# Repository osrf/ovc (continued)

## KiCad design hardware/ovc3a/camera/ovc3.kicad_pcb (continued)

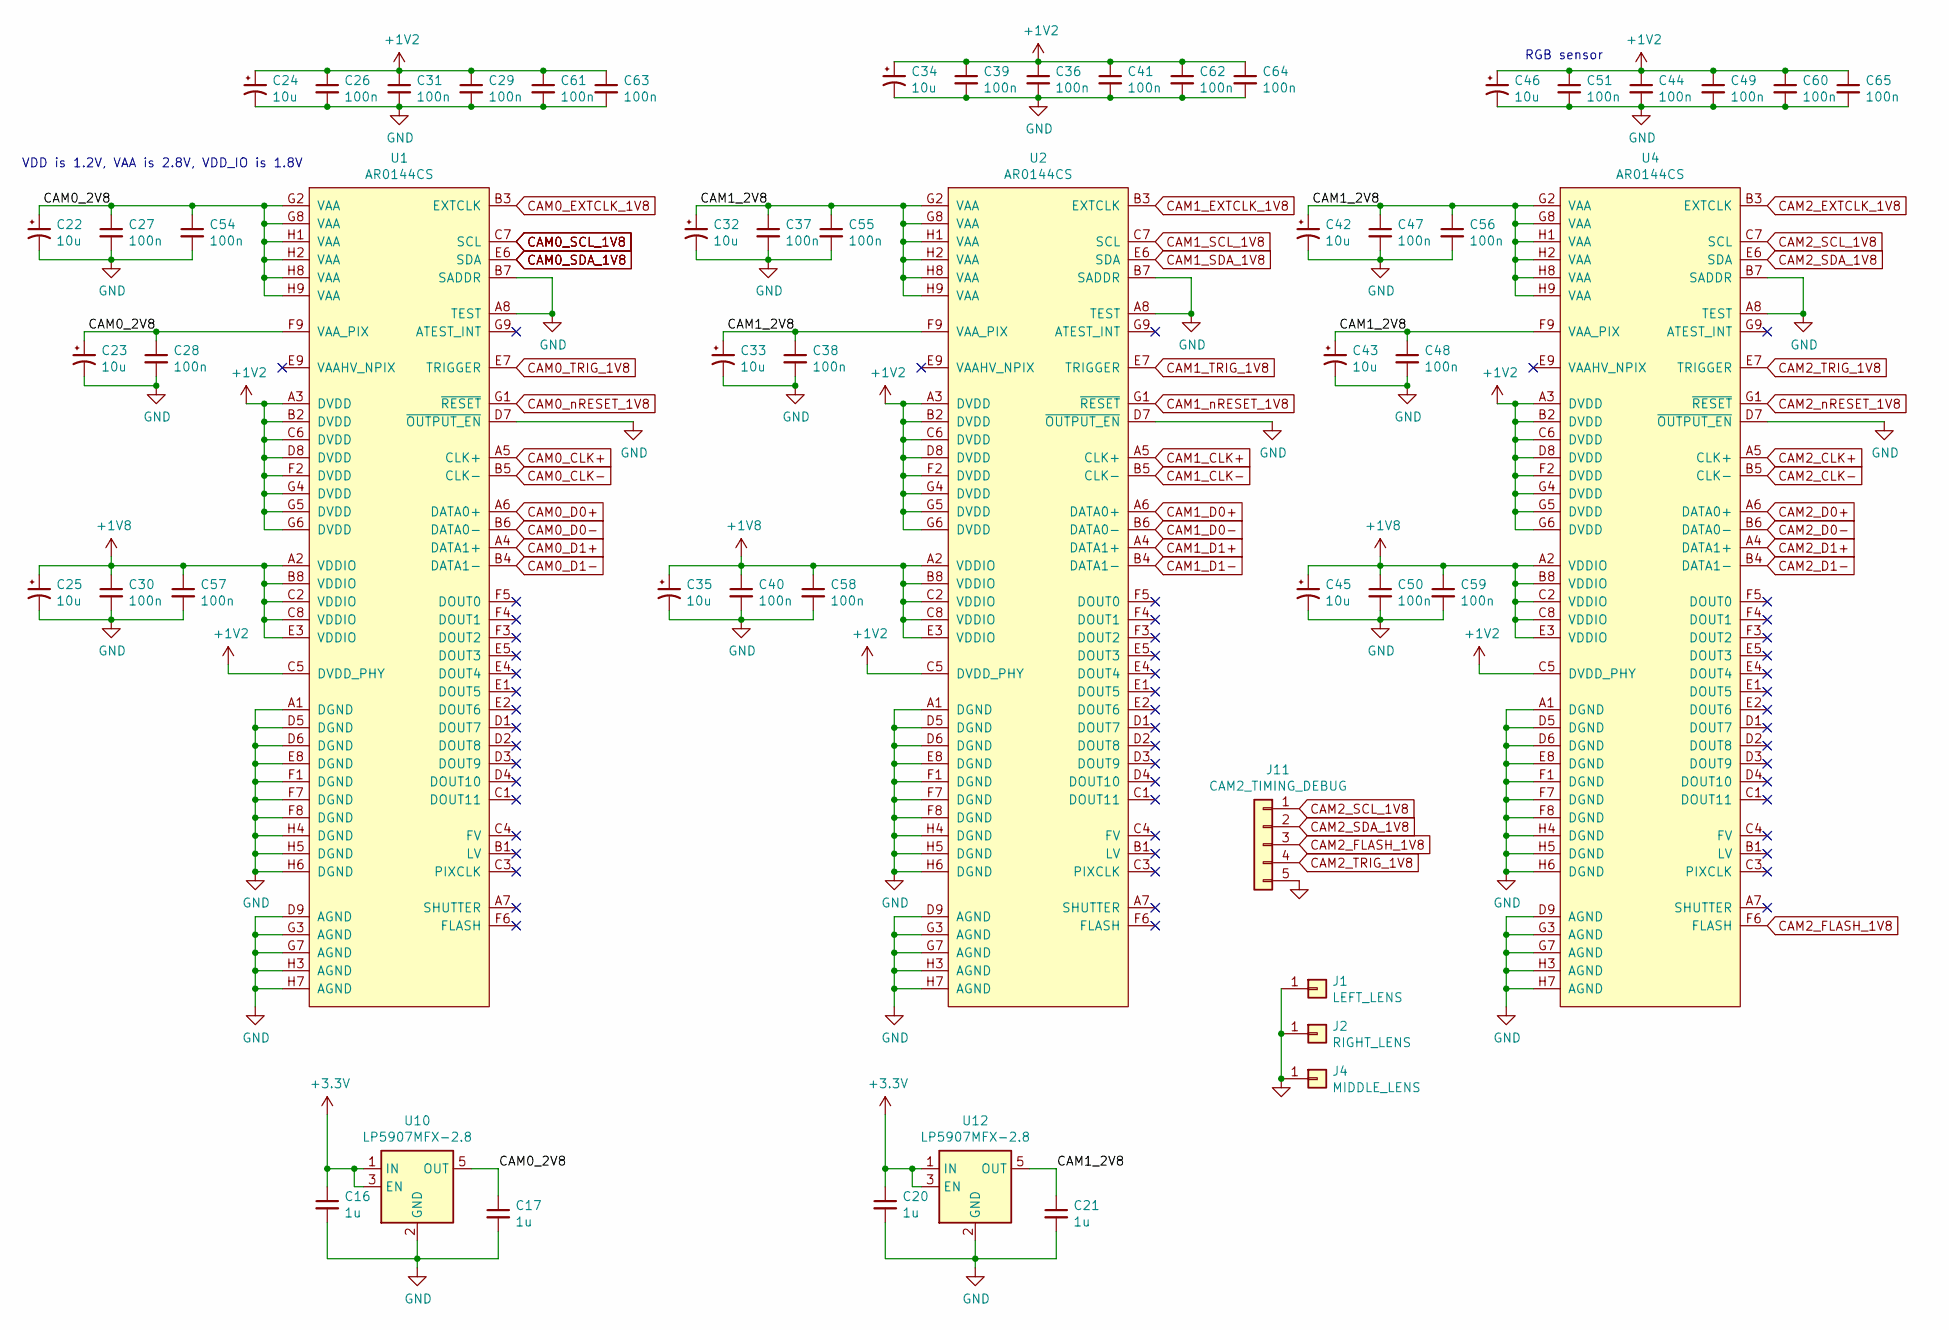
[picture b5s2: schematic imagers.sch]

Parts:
C16, C17, C20, C21: 1u; C_0402_1005Metric; MPN CL05A105KA5NQNC
C22, C23, C24, C25, C32, C33, C34, C35, C42, C43, C45, C46: 10u; C_0402_1005Metric; MPN CL05A106MP8NUB8
C26, C27, C28, C29, C30, C31, C36, C37, C38, C39, C40, C41, C44, C47, C48, C49, C50, C51, C54, C55, C56, C57, C58, C59, C60, C61, C62, C63, C64, C65: 100n; C_0402_1005Metric; MPN CL05F104ZO5NNNC
J1: LEFT_LENS; LENS_HOLDER_20MM_PT-LH010M; MPN DNP
J2: RIGHT_LENS; LENS_HOLDER_20MM_PT-LH010M; MPN DNP
J4: MIDDLE_LENS; LENS_HOLDER_20MM_PT-LH010M; MPN DNP
J11: CAM2_TIMING_DEBUG; PinHeader_1x05_P2.00mm_Vertical; MPN DNP
U1, U2: AR0144CS; BGA-72_9x8_5.545x5.565mm; MPN AR0144CSSM00SUKA0-CPBR2
U4: AR0144CS; BGA-72_9x8_5.545x5.565mm; MPN AR0144CSSC00SUKA0-CPBR2
U10, U12: LP5907MFX-2.8; SOT-23-5; MPN LP5907MFX-2.8/NOPB

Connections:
+1V2: C24.1, C26.1, C29.1, C31.1, C34.1, C36.1, C39.1, C41.1, C44.1, C46.1, C49.1, C51.1, C60.1, C61.1, C62.1, C63.1, C64.1, C65.1, U1.A3 (DVDD), U1.B2 (DVDD), U1.C5 (DVDD_PHY), U1.C6 (DVDD), U1.D8 (DVDD), U1.F2 (DVDD), U1.G4 (DVDD), U1.G5 (DVDD), U1.G6 (DVDD), U2.A3 (DVDD), U2.B2 (DVDD), U2.C5 (DVDD_PHY), U2.C6 (DVDD), U2.D8 (DVDD), U2.F2 (DVDD), U2.G4 (DVDD), U2.G5 (DVDD), U2.G6 (DVDD), U4.A3 (DVDD), U4.B2 (DVDD), U4.C5 (DVDD_PHY), U4.C6 (DVDD), U4.D8 (DVDD), U4.F2 (DVDD), U4.G4 (DVDD), U4.G5 (DVDD), U4.G6 (DVDD); also elsewhere on the board
+1V8: C25.1, C30.1, C35.1, C40.1, C45.1, C50.1, C57.1, C58.1, C59.1, U1.A2 (VDDIO), U1.B8 (VDDIO), U1.C2 (VDDIO), U1.C8 (VDDIO), U1.E3 (VDDIO), U2.A2 (VDDIO), U2.B8 (VDDIO), U2.C2 (VDDIO), U2.C8 (VDDIO), U2.E3 (VDDIO), U4.A2 (VDDIO), U4.B8 (VDDIO), U4.C2 (VDDIO), U4.C8 (VDDIO), U4.E3 (VDDIO); also elsewhere on the board
/imagers/CAM0_2V8: C17.1, C22.1, C23.1, C27.1, C28.1, C54.1, U1.F9 (VAA_PIX), U1.G2 (VAA), U1.G8 (VAA), U1.H1 (VAA), U1.H2 (VAA), U1.H8 (VAA), U1.H9 (VAA), U10.5 (OUT)
/imagers/CAM1_2V8: C21.1, C32.1, C33.1, C37.1, C38.1, C42.1, C43.1, C47.1, C48.1, C55.1, C56.1, U2.F9 (VAA_PIX), U2.G2 (VAA), U2.G8 (VAA), U2.H1 (VAA), U2.H2 (VAA), U2.H8 (VAA), U2.H9 (VAA), U4.F9 (VAA_PIX), U4.G2 (VAA), U4.G8 (VAA), U4.H1 (VAA), U4.H2 (VAA), U4.H8 (VAA), U4.H9 (VAA), U12.5 (OUT)
CAM0_CLK+: U1.A5 (CLK+); also elsewhere on the board
CAM0_CLK-: U1.B5 (CLK-); also elsewhere on the board
CAM0_D0+: U1.A6 (DATA0+); also elsewhere on the board
CAM0_D0-: U1.B6 (DATA0-); also elsewhere on the board
CAM0_D1+: U1.A4 (DATA1+)
CAM0_D1-: U1.B4 (DATA1-)
CAM0_EXTCLK_1V8: U1.B3 (EXTCLK); also elsewhere on the board
CAM0_SCL_1V8: U1.C7 (SCL); also elsewhere on the board
CAM0_SDA_1V8: U1.E6 (SDA); also elsewhere on the board
CAM0_TRIG_1V8: U1.E7 (TRIGGER); also elsewhere on the board
CAM0_nRESET_1V8: U1.G1 (~RESET); also elsewhere on the board
CAM1_CLK+: U2.A5 (CLK+); also elsewhere on the board
CAM1_CLK-: U2.B5 (CLK-); also elsewhere on the board
CAM1_D0+: U2.A6 (DATA0+); also elsewhere on the board
CAM1_D0-: U2.B6 (DATA0-); also elsewhere on the board
CAM1_D1+: U2.A4 (DATA1+)
CAM1_D1-: U2.B4 (DATA1-)
CAM1_EXTCLK_1V8: U2.B3 (EXTCLK); also elsewhere on the board
CAM1_SCL_1V8: U2.C7 (SCL); also elsewhere on the board
CAM1_SDA_1V8: U2.E6 (SDA); also elsewhere on the board
CAM1_TRIG_1V8: U2.E7 (TRIGGER); also elsewhere on the board
CAM1_nRESET_1V8: U2.G1 (~RESET); also elsewhere on the board
CAM2_CLK+: U4.A5 (CLK+); also elsewhere on the board
CAM2_CLK-: U4.B5 (CLK-); also elsewhere on the board
CAM2_D0+: U4.A6 (DATA0+); also elsewhere on the board
CAM2_D0-: U4.B6 (DATA0-); also elsewhere on the board
CAM2_D1+: U4.A4 (DATA1+)
CAM2_D1-: U4.B4 (DATA1-)
CAM2_EXTCLK_1V8: U4.B3 (EXTCLK); also elsewhere on the board
CAM2_FLASH_1V8: J11.3, U4.F6 (FLASH)
CAM2_SCL_1V8: J11.1, U4.C7 (SCL); also elsewhere on the board
CAM2_SDA_1V8: J11.2, U4.E6 (SDA); also elsewhere on the board
CAM2_TRIG_1V8: J11.4, U4.E7 (TRIGGER); also elsewhere on the board
CAM2_nRESET_1V8: U4.G1 (~RESET); also elsewhere on the board
GND: C16.2, C17.2, C20.2, C21.2, C22.2, C23.2, C24.2, C25.2, C26.2, C27.2, C28.2, C29.2, C30.2, C31.2, C32.2, C33.2, C34.2, C35.2, C36.2, C37.2, C38.2, C39.2, C40.2, C41.2, C42.2, C43.2, C44.2, C45.2, C46.2, C47.2, C48.2, C49.2, C50.2, C51.2, C54.2, C55.2, C56.2, C57.2, C58.2, C59.2, C60.2, C61.2, C62.2, C63.2, C64.2, C65.2, J1.1, J2.1, J4.1, J11.5, U1.A1 (DGND), U1.A8 (TEST), U1.B7 (SADDR), U1.D5 (DGND), U1.D6 (DGND), U1.D7 (~OUTPUT_EN), U1.D9 (AGND), U1.E8 (DGND), U1.F1 (DGND), U1.F7 (DGND), U1.F8 (DGND), U1.G3 (AGND), U1.G7 (AGND), U1.H3 (AGND), U1.H4 (DGND), U1.H5 (DGND), U1.H6 (DGND), U1.H7 (AGND), U2.A1 (DGND), U2.A8 (TEST), U2.B7 (SADDR), U2.D5 (DGND), U2.D6 (DGND), U2.D7 (~OUTPUT_EN), U2.D9 (AGND), U2.E8 (DGND), U2.F1 (DGND), U2.F7 (DGND), U2.F8 (DGND), U2.G3 (AGND), U2.G7 (AGND), U2.H3 (AGND), U2.H4 (DGND), U2.H5 (DGND), U2.H6 (DGND), U2.H7 (AGND), U4.A1 (DGND), U4.A8 (TEST), U4.B7 (SADDR), U4.D5 (DGND), U4.D6 (DGND), U4.D7 (~OUTPUT_EN), U4.D9 (AGND), U4.E8 (DGND), U4.F1 (DGND), U4.F7 (DGND), U4.F8 (DGND), U4.G3 (AGND), U4.G7 (AGND), U4.H3 (AGND), U4.H4 (DGND), U4.H5 (DGND), U4.H6 (DGND), U4.H7 (AGND), U10.2 (GND), U12.2 (GND); also elsewhere on the board

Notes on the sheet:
VDD is 1.2V, VAA is 2.8V, VDD_IO is 1.8V
RGB sensor

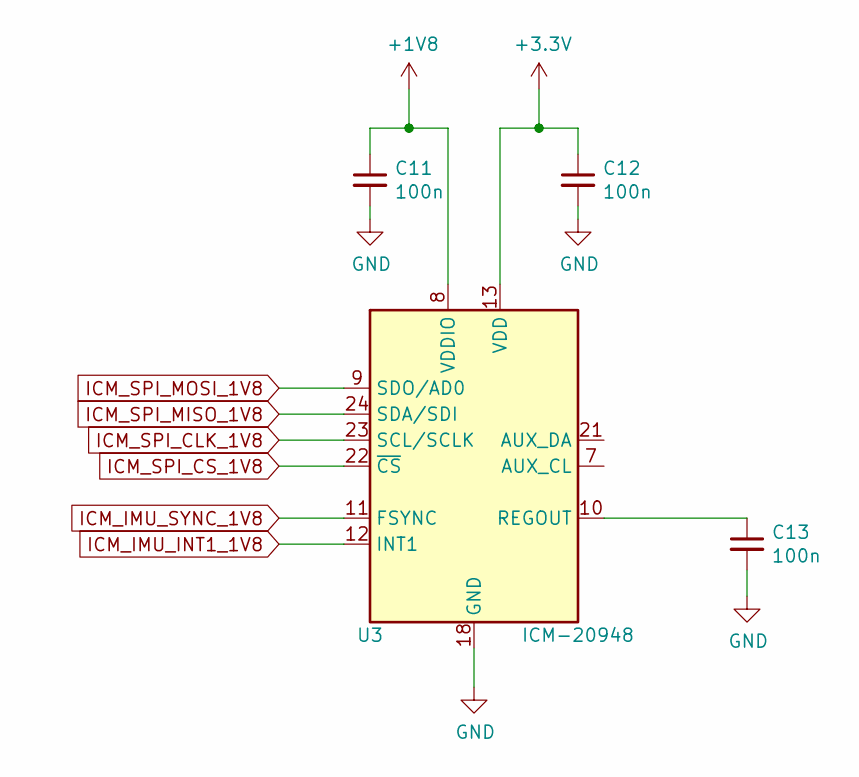
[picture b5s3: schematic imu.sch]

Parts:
C11, C12, C13: 100n; C_0402_1005Metric; MPN CL05F104ZO5NNNC
U3: ICM-20948; InvenSense_QFN-24_3x3mm_P0.4mm; MPN ICM-20948

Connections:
+1V8: C11.1, U3.8 (VDDIO); also elsewhere on the board
GND: C11.2, C12.2, C13.2, U3.18 (GND), U3.20 (GND); also elsewhere on the board
ICM_IMU_INT1_1V8: U3.12 (INT1); also elsewhere on the board
ICM_IMU_SYNC_1V8: U3.11 (FSYNC); also elsewhere on the board
ICM_SPI_CLK_1V8: U3.23 (SCL/SCLK); also elsewhere on the board
ICM_SPI_CS_1V8: U3.22 (~CS); also elsewhere on the board
ICM_SPI_MISO_1V8: U3.24 (SDA/SDI); also elsewhere on the board
ICM_SPI_MOSI_1V8: U3.9 (SDO/AD0); also elsewhere on the board
unnamed: C13.1, U3.10 (REGOUT)

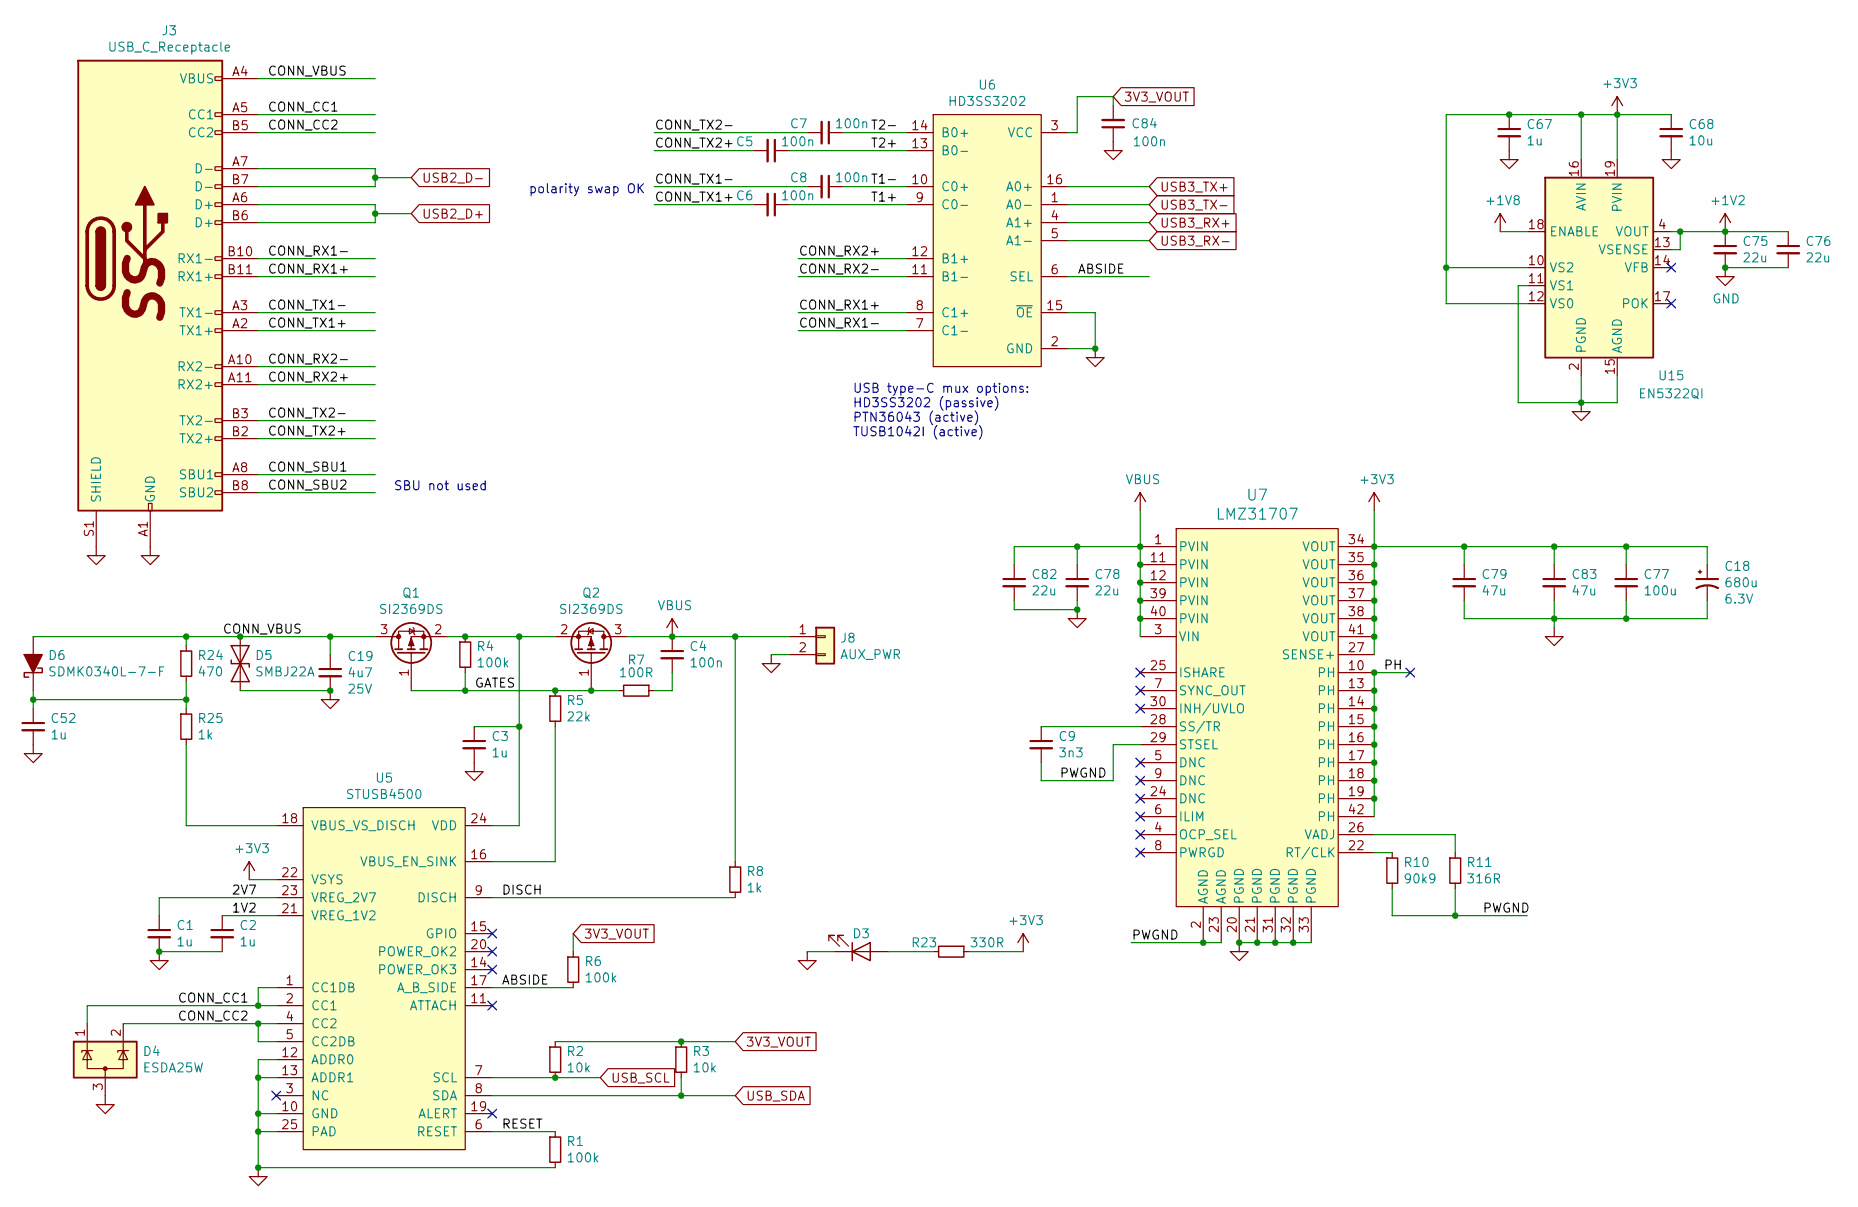
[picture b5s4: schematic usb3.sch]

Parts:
C1, C2, C3, C52, C67: 1u; C_0402_1005Metric; MPN CL05A105KA5NQNC
C4, C5, C6, C7, C8, C84: 100n; C_0402_1005Metric; MPN CL05F104ZO5NNNC
C9: 3n3; C_0402_1005Metric; MPN CL05B332KB5NNNC
C18: 680u; CP_Elec_6.3x7.7; voltage 6.3V; MPN EEE-FTJ681XAP
C19: 4u7; C_0603_1608Metric; voltage 25V; MPN CL10A475KA8NQNC
C68: 10u; C_0402_1005Metric; MPN CL05A106MP8NUB8
C75, C76: 22u; C_0603_1608Metric; MPN GRM188R60J226MEA0D
C77: 100u; C_1206_3216Metric; MPN GRM31CR60J107ME39K
C78, C82: 22u; C_1206_3216Metric; MPN CL31A226KAHNNNE
C79, C83: 47u; C_1206_3216Metric; MPN CL31A476MQHNNNE
D3: LED; LED_0402_1005Metric; MPN VLMS1500-GS08
D4: ESDA25W; SOT-23; MPN ESDA25W
D5: SMBJ22A; D_SMB; MPN SMBJ22A
D6: SDMK0340L-7-F; D_SOD-323; MPN SDMK0340L-7-F
J3: USB_C_Receptacle; USB_C_Receptacle_Wurth_632723300011; MPN 632723300011
J8: AUX_PWR; Molex_Nano-Fit_105313-xx02_1x02_P2.50mm_Horizontal; MPN 1053131102
Q1, Q2: SI2369DS; SOT-23; MPN SI2369DS-T1-GE3
R1, R4, R6: 100k; R_0402_1005Metric; MPN ERA-2AED104X
R2, R3: 10k; R_0402_1005Metric; MPN ERA-2AED103X
R5: 22k; R_0402_1005Metric; MPN ERJ-2RKF2202X
R7: 100R; R_0402_1005Metric; MPN ERA-2AED101X
R8: 1k; R_0603_1608Metric; MPN ESR03EZPJ102
R10: 90k9; R_0402_1005Metric; MPN ERA-2AEB9092X
R11: 316R; R_0402_1005Metric; MPN ERJ-2RKF3160X
R23: 330R; R_0402_1005Metric; MPN ERJ-2GEJ331X
R24: 470; R_0402_1005Metric; MPN ERJ-2RKF4700X
R25: 1k; R_0402_1005Metric; MPN ERJ-2RKF1001X
U5: STUSB4500; QFN-24-1EP_4x4mm_P0.5mm_EP2.7x2.7mm; MPN STUSB4500QTR
U6: HD3SS3202; TI_R_PUQFN_N16; MPN HD3SS3202IRSVR
U7: LMZ31707; TI_RVQ_42; MPN LMZ31707RVQR
U15: EN5322QI; Converter_DCDC_Intel_QFN-24_4x6mm_P0.65mm_ThermalVias; MPN EN5322QI

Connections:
3V3_VOUT: C84.2, R2.1, R3.1, R6.1, U6.3 (VCC); also elsewhere on the board
+1V2: C75.1, C76.1, U15.4 (VOUT), U15.5 (VOUT), U15.6 (VOUT), U15.7 (VOUT), U15.13 (VSENSE); also elsewhere on the board
+1V8: U15.18 (ENABLE); also elsewhere on the board
/usb3/1V2: C2.1, U5.21 (VREG_1V2)
/usb3/2V7: C1.1, U5.23 (VREG_2V7)
/usb3/ABSIDE: R6.2, U5.17 (A_B_SIDE), U6.6 (SEL)
/usb3/CONN_CC1: D4.1 (K), J3.A5 (CC1), U5.1 (CC1DB), U5.2 (CC1)
/usb3/CONN_CC2: D4.2 (K), J3.B5 (CC2), U5.4 (CC2), U5.5 (CC2DB)
/usb3/CONN_RX1+: J3.B11 (RX1+), U6.8 (C1+)
/usb3/CONN_RX1-: J3.B10 (RX1-), U6.7 (C1-)
/usb3/CONN_RX2+: J3.A11 (RX2+), U6.12 (B1+)
/usb3/CONN_RX2-: J3.A10 (RX2-), U6.11 (B1-)
/usb3/CONN_SBU1: J3.A8 (SBU1)
/usb3/CONN_SBU2: J3.B8 (SBU2)
/usb3/CONN_TX1+: C6.2, J3.A2 (TX1+)
/usb3/CONN_TX1-: C8.2, J3.A3 (TX1-)
/usb3/CONN_TX2+: C5.2, J3.B2 (TX2+)
/usb3/CONN_TX2-: C7.2, J3.B3 (TX2-)
/usb3/CONN_VBUS: C19.1, D5.1 (A1), D6.2 (A), J3.A4 (VBUS), J3.A9 (VBUS), J3.B4 (VBUS), J3.B9 (VBUS), Q1.3 (D), R24.1
/usb3/DISCH: R8.2, U5.9 (DISCH)
/usb3/GATES: Q1.1 (G), Q2.1 (G), R4.2, R5.1, R7.2
/usb3/PH: U7.10 (PH), U7.13 (PH), U7.14 (PH), U7.15 (PH), U7.16 (PH), U7.17 (PH), U7.18 (PH), U7.19 (PH), U7.42 (PH)
/usb3/PWGND: C9.2, R10.2, R11.2, U7.2 (AGND), U7.23 (AGND), U7.29 (STSEL)
/usb3/RESET: R1.1, U5.6 (RESET)
/usb3/T1+: C6.1, U6.9 (C0-)
/usb3/T1-: C8.1, U6.10 (C0+)
/usb3/T2+: C5.1, U6.13 (B0-)
/usb3/T2-: C7.1, U6.14 (B0+)
GND: C1.2, C2.2, C3.2, C18.2, C19.2, C52.2, C67.2, C68.2, C75.2, C76.2, C77.2, C78.2, C79.2, C82.2, C83.2, C84.1, D3.1 (K), D4.3 (A), D5.2 (A2), J3.A1 (GND), J3.A12 (GND), J3.B1 (GND), J3.B12 (GND), J3.S1 (SHIELD), J8.2, R1.2, U5.10 (GND), U5.12 (ADDR0), U5.13 (ADDR1), U5.25 (PAD), U6.2 (GND), U6.15 (~OE), U7.20 (PGND), U7.21 (PGND), U7.31 (PGND), U7.32 (PGND), U7.33 (PGND), U15.2 (PGND), U15.3 (PGND), U15.8 (PGND), U15.9 (PGND), U15.11 (VS1), U15.15 (AGND), U15.25 (PGND); also elsewhere on the board
unnamed: C3.1, Q1.2 (S), Q2.2 (S), R4.1, U5.24 (VDD)
unnamed: C4.2, R7.1
unnamed: C9.1, U7.28 (SS/TR)
unnamed: C52.1, D6.1 (K), R24.2, R25.1
unnamed: D3.2 (A), R23.2
unnamed: R5.2, U5.16 (VBUS_EN_SINK)
unnamed: R10.1, U7.22 (RT/CLK)
unnamed: R11.1, U7.26 (VADJ)
unnamed: R25.2, U5.18 (VBUS_VS_DISCH)
USB2_D+: J3.A6 (D+), J3.B6 (D+); also elsewhere on the board
USB2_D-: J3.A7 (D-), J3.B7 (D-); also elsewhere on the board
USB3_RX+: U6.4 (A1+); also elsewhere on the board
USB3_RX-: U6.5 (A1-); also elsewhere on the board
USB3_TX+: U6.16 (A0+); also elsewhere on the board
USB3_TX-: U6.1 (A0-); also elsewhere on the board
USB_SCL: R2.2, U5.7 (SCL); also elsewhere on the board
USB_SDA: R3.2, U5.8 (SDA); also elsewhere on the board
VBUS: C4.1, C78.1, C82.1, J8.1, Q2.3 (D), R8.1, U7.1 (PVIN), U7.3 (VIN), U7.11 (PVIN), U7.12 (PVIN), U7.39 (PVIN), U7.40 (PVIN)

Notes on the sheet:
USB type-C mux options: HD3SS3202 (passive) PTN36043 (active) TUSB1042I (active)
polarity swap OK
SBU not used
